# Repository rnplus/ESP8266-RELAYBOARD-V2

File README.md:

# esp8266-relayboard-pka
New ESP8266 based wifi relay board. Has 3 relay switches and a BMP180 air pressure sensor

# Versions
Revision 1 is the version that I built. There is a small mistake in the schematic: the pull-up resistor of the reset pin is on the wrong side of the jumper that selects which function the reset/gpio2 button has.
I fixed this mistake in revision 2 but I did not test that new version of the design, so use at your own risk.

License: CC BY-SA 3.0

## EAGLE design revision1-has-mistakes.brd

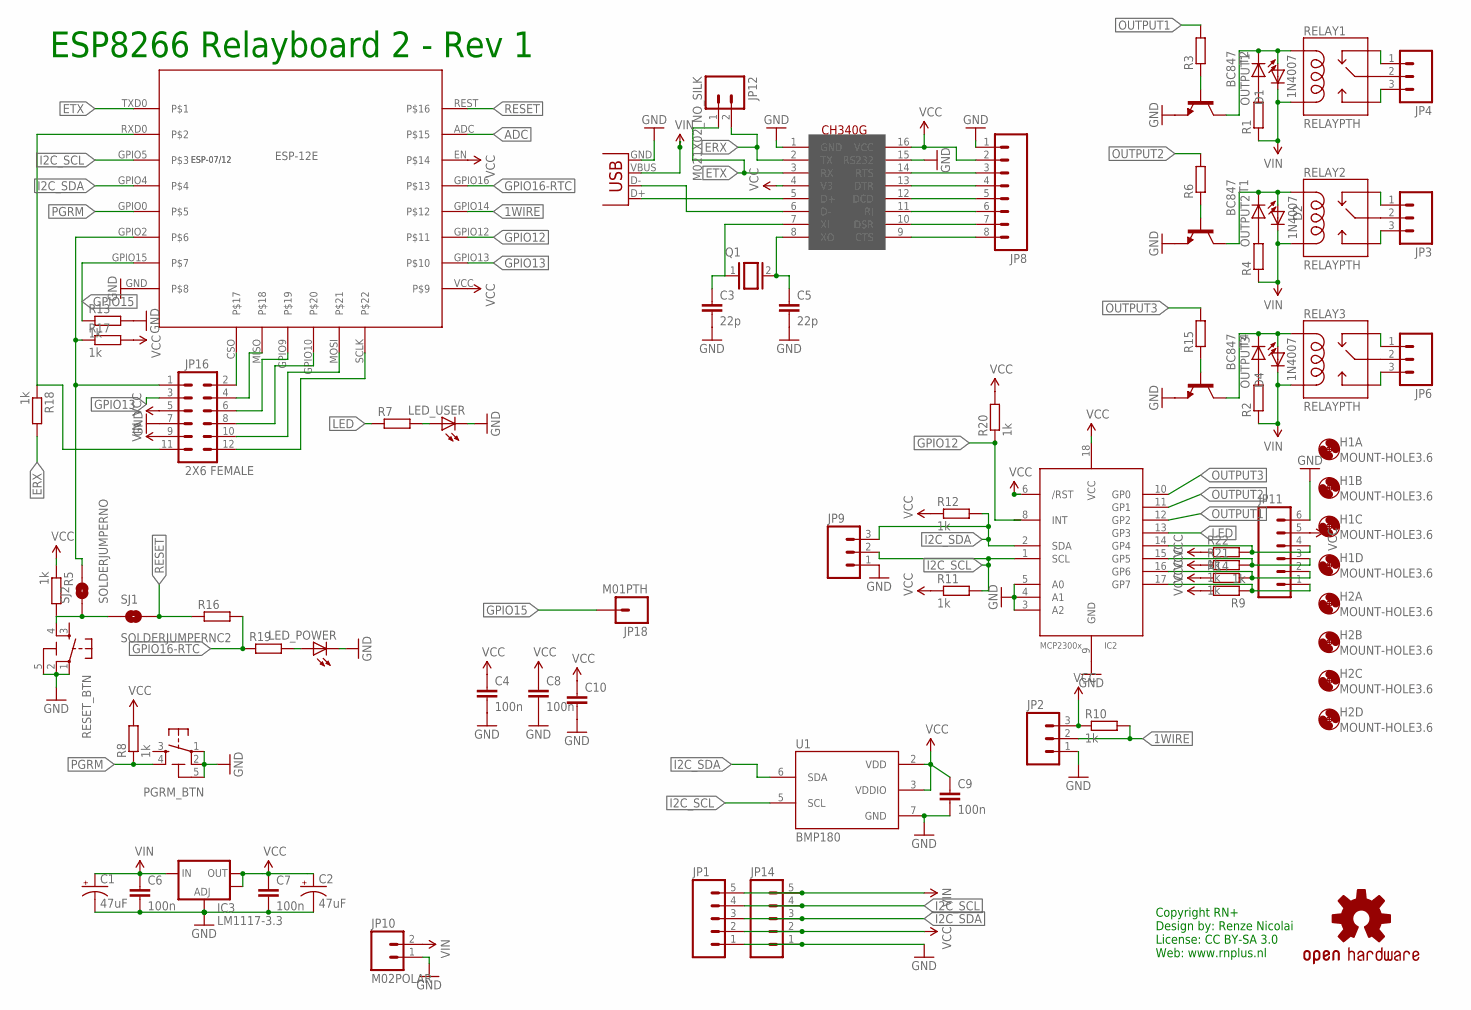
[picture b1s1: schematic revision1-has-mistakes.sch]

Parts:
C1, C2: 47uF; PANASONIC_D
C3, C5: 22p; C0805K
C4, C6, C7, C8, C9: 100n; C0805K
C10: C-EUC0805K; C0805K
D1, D2, D4: 1N4942; DO41-10
H1A, H1B, H1C, H1D, H2A, H2B, H2C, H2D: MOUNT-HOLE3.6; 3,6
IC2: MCP23008/SO; SO18W
IC3: LM1117-3.3; SOT223
JP1, JP14: M05PTH; 1X05
JP2: M03LONGPADS; 1X03_LONGPADS
JP3, JP4, JP6: M03-SCREW-5MM; SCREWTERMINAL-5MM-3
JP5: USB-B; USB-B-PTH
JP8: M08SILK_FEMALE_PTH; 1X08
JP9: M031X03_NO_SILK; 1X03_NO_SILK
JP10: M02POLAR; MOLEX-1X2
JP11: M06LONGPADS; 1X06_LONGPADS
JP12: M021X02_NO_SILK; 1X02_NO_SILK
JP16: 2X6 FEMALE; 2X6
JP18: M01PTH; 1X01
LED_POWER: LEDCHIP-LED0805; CHIP-LED0805
LED_USER: LEDCHIP-LED0805; CHIP-LED0805
LOGO1: OSHW-LOGOL; OSHW-LOGO-L
OUTPUT1, OUTPUT2, OUTPUT3: LEDCHIP-LED0805; CHIP-LED0805
PGRM_BTN: SMARTPRJ_TS42
Q1: XTAL/S; QS
R1, R2, R3, R4, R6, R7, R15, R16, R19: SMARTPRJ_R-EU_M0805; SMARTPRJ_M0805
R5, R8, R9, R10, R11, R12, R13, R14, R17, R18, R20, R21, R22: 1k; SMARTPRJ_M0805
RELAY1, RELAY2, RELAY3: RELAYPTH; SRD-05VDC-SL-C
RESET_BTN: SMARTPRJ_TS42
SJ1: SOLDERJUMPERNC2; SJ_2S-NOTRACE
SJ2: SOLDERJUMPERNO; SJ_2S-NO
T1, T2, T4: BC847; SOT23
U1: BMP180
U$1: CH340G; SOIC16
U$2: ESP-07/12_ESP-12E; ESP-07/12

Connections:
1WIRE: JP2.2, R10.2, U$2.GPIO14
ADC: U$2.ADC
ERX: JP12.2, R18.2, U$1.2 (TX)
ERXR: JP16.11, R18.1, U$2.RXD0
ETX: JP12.1, U$1.3 (RX), U$2.TXD0
GND: C1.-, C2.-, C3.2, C4.2, C5.2, C6.2, C7.2, C8.2, C9.2, C10.2, IC2.3 (A2), IC2.4 (A1), IC2.5 (A0), IC2.9 (GND), IC3.1 (ADJ), JP1.1, JP2.1, JP5.GND, JP8.1, JP9.1, JP10.1, JP11.6, JP14.1, JP16.7, LED_POWER.C, LED_USER.C, PGRM_BTN.1, PGRM_BTN.2, PGRM_BTN.5 (5-GND), R13.2, RESET_BTN.1, RESET_BTN.2, RESET_BTN.5 (5-GND), T1.2 (E), T2.2 (E), T4.2 (E), U1.7 (GND), U$1.1 (GND), U$1.15 (RS232), U$2.GND
GPIO12: IC2.8 (INT), R20.1, U$2.GPIO12
GPIO13: JP16.3, U$2.GPIO13
GPIO15: JP18.1, R13.1, U$2.GPIO15
GPIO16-RTC: R16.2, R19.1, U$2.GPIO16
I2C_SCL: IC2.1 (SCL), JP1.4, JP9.2, JP14.4, R11.2, U1.5 (SCL), U$2.GPIO5
I2C_SDA: IC2.2 (SDA), JP1.3, JP9.3, JP14.3, R12.2, U1.6 (SDA), U$2.GPIO4
LED: IC2.13 (GP3), R7.1
unnamed: D2.A, OUTPUT2.C, RELAY2.COIL1, T1.3 (C)
unnamed: D1.A, OUTPUT1.C, RELAY1.COIL1, T2.3 (C)
unnamed: JP3.2, RELAY2.SWCOMMON
unnamed: JP4.2, RELAY1.SWCOMMON
unnamed: JP4.1, RELAY1.SWCLOSED (SWCLOSE)
unnamed: JP4.3, RELAY1.SWOPEN
unnamed: JP3.3, RELAY2.SWOPEN
unnamed: JP3.1, RELAY2.SWCLOSED (SWCLOSE)
unnamed: R3.1, T2.1 (B)
unnamed: R6.1, T1.1 (B)
unnamed: R5.2, RESET_BTN.4, SJ1.1, SJ2.1
unnamed: OUTPUT2.A, R4.2
unnamed: IC2.14 (GP4), JP11.4, R22.2
unnamed: LED_USER.A, R7.2
unnamed: OUTPUT1.A, R1.2
unnamed: D4.A, OUTPUT3.C, RELAY3.COIL1, T4.3 (C)
unnamed: R15.1, T4.1 (B)
unnamed: IC2.15 (GP5), JP11.3, R21.2
unnamed: C3.1, Q1.1, U$1.7 (XI)
unnamed: OUTPUT3.A, R2.2
unnamed: C5.1, Q1.2, U$1.8 (XO)
unnamed: JP6.2, RELAY3.SWCOMMON
unnamed: JP6.1, RELAY3.SWCLOSED (SWCLOSE)
unnamed: JP6.3, RELAY3.SWOPEN
unnamed: JP8.5, U$1.12 (DCD)
unnamed: JP8.4, U$1.13 (DTR)
unnamed: JP8.3, U$1.14 (RTS)
unnamed: JP8.8, U$1.9 (CTS)
unnamed: JP8.7, U$1.10 (DSR)
unnamed: JP8.6, U$1.11 (RI)
unnamed: LED_POWER.A, R19.2
unnamed: JP16.2, U$2.CSO
unnamed: JP16.4, U$2.MISO
unnamed: JP16.6, U$2.GPIO9
unnamed: JP16.8, U$2.GPIO10
unnamed: JP16.10, U$2.MOSI
unnamed: JP16.12, U$2.SCLK
unnamed: JP16.1, R17.1, SJ2.2, U$2.GPIO2
OUTPUT1: IC2.12 (GP2), R3.2
OUTPUT2: IC2.11 (GP1), R6.2
OUTPUT3: IC2.10 (GP0), R15.2
PGRM: PGRM_BTN.4, R8.1, U$2.GPIO0
RESET: R16.1, SJ1.2, U$2.REST
SENSOR1: IC2.16 (GP6), JP11.2, R14.2
SENSOR2: IC2.17 (GP7), JP11.1, R9.1
USB_N: JP5.D-, U$1.6 (D-)
USB_P: JP5.D+, U$1.5 (D+)
VCC: C2.+, C4.1, C7.1, C8.1, C9.1, C10.1, IC2.6 (/RST), IC2.18 (VCC), IC3.2 (OUT), IC3.4 (OUT), JP1.2, JP2.3, JP8.2, JP11.5, JP14.2, JP16.5, R5.1, R8.2, R9.2, R10.1, R11.1, R12.1, R14.1, R17.2, R20.2, R21.1, R22.1, U1.2 (VDD), U1.3 (VDDIO), U$1.4 (V3), U$1.16 (VCC), U$2.EN, U$2.VCC
VIN: C1.+, C6.1, D1.C, D2.C, D4.C, IC3.3 (IN), JP1.5, JP5.VBUS, JP10.2, JP14.5, JP16.9, R1.1, R2.1, R4.1, RELAY1.COIL0, RELAY2.COIL0, RELAY3.COIL0

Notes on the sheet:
Copyright RN+ Design by: Renze Nicolai License: CC BY-SA 3.0 Web: www.rnplus.nl
ESP8266 Relayboard 2 - Rev 1
1N4007

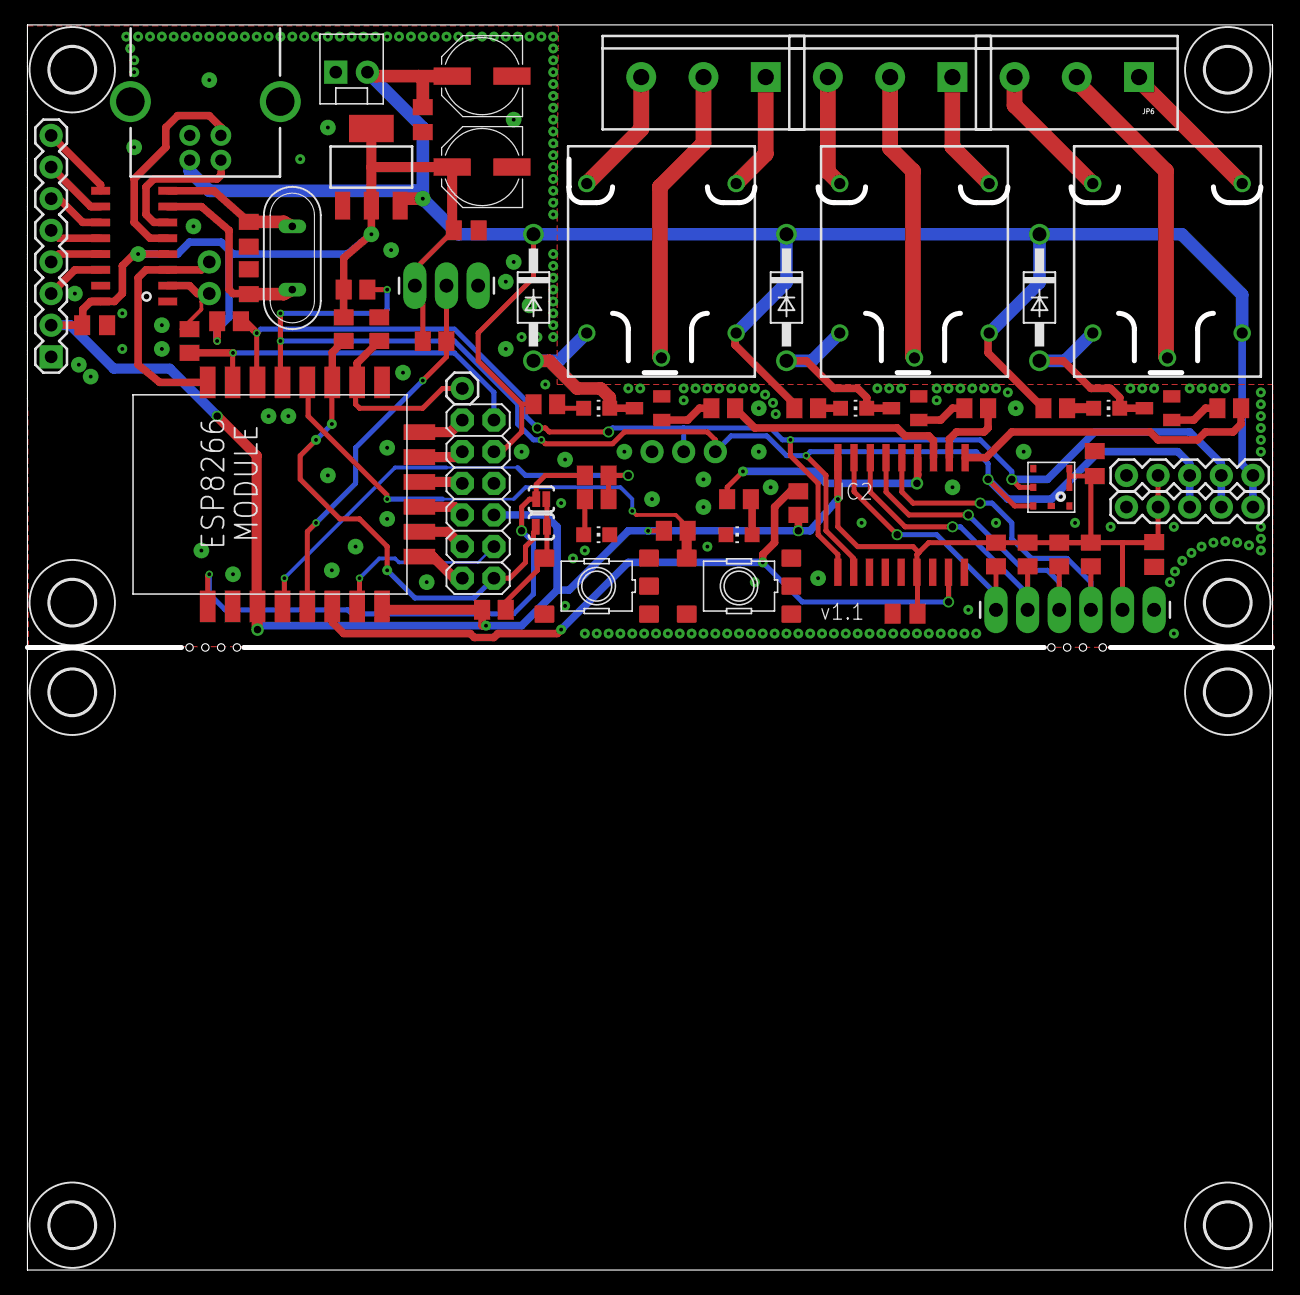
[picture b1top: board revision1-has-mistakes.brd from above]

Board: 2 copper layers, 100.0 x 99.6 mm, 79 parts (1 on the bottom side), 61 nets.

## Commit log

2016-01-08 CC BY-SA 3.0
2016-03-04 Photo and readme

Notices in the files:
parts and their libraries:
SparkFun-PowerIC: Licensing: Creative Commons ShareAlike 4.0 International - https://creativecommons.org/licenses/by-sa/4.0
